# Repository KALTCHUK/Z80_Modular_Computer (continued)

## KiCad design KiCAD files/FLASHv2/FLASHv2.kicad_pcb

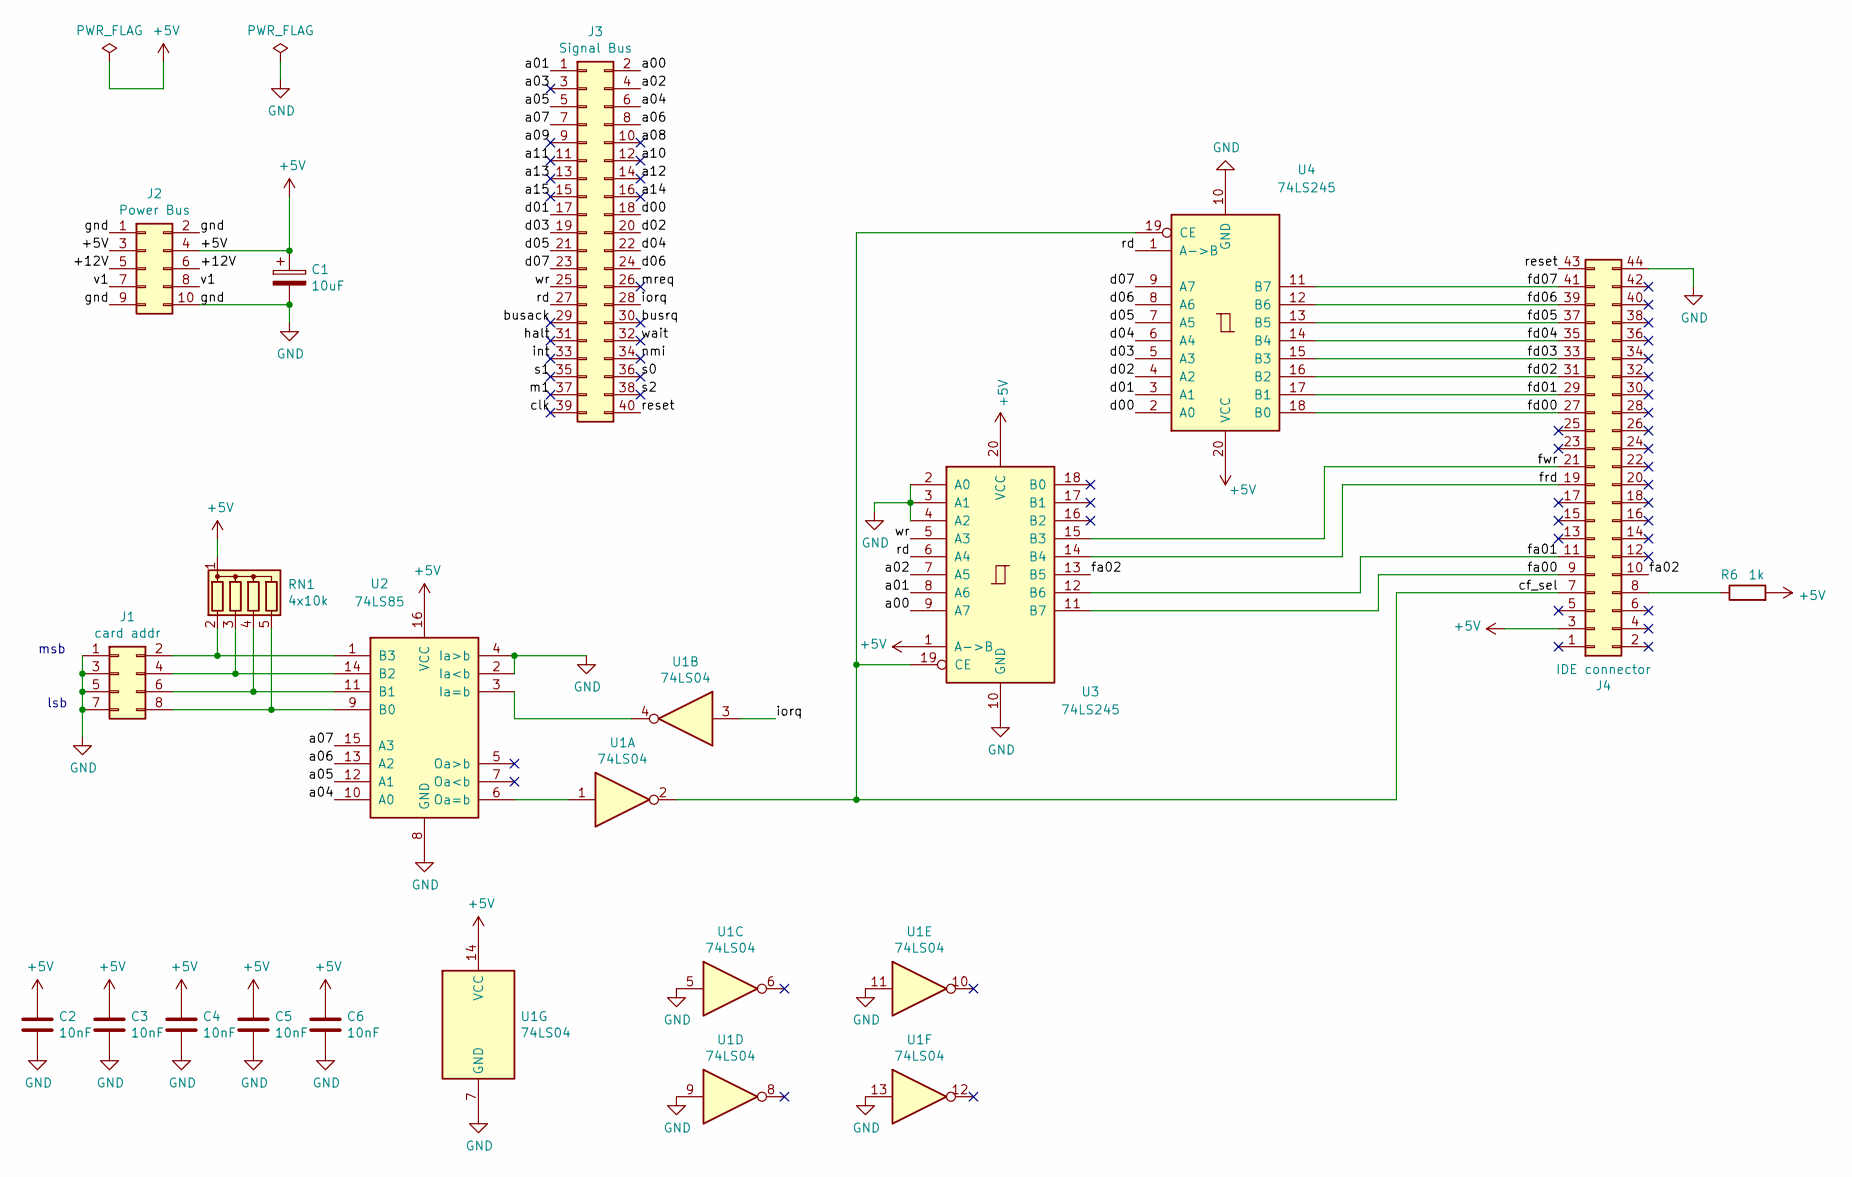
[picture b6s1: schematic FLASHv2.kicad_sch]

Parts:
C1: 10uF; CP_Radial_D5.0mm_P2.50mm
C2, C3, C4, C5, C6: 10nF; C_Disc_D3.8mm_W2.6mm_P2.50mm
J1: card addr; PinHeader_2x04_P2.54mm_Vertical
J2: Power Bus; PinHeader_2x05_P2.54mm_Vertical
J3: Signal Bus; PinHeader_2x20_P2.54mm_Vertical
J4: IDE connector; PinHeader_2x22_P2.00mm_Vertical
R6: 1k; R_Axial_DIN0207_L6.3mm_D2.5mm_P10.16mm_Horizontal
RN1: 4x10k; R_Array_SIP5
U1: 74LS04; DIP-14_W7.62mm_Socket_LongPads
U2: 74LS85; DIP-16_W7.62mm_Socket_LongPads
U3, U4: 74LS245; DIP-20_W7.62mm_Socket_LongPads

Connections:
+5V: C1.1, C2.1, C3.1, C4.1, C5.1, C6.1, J2.3, J2.4, J4.3, R6.2, RN1.1 (common), U1.14 (VCC), U2.16 (VCC), U3.1 (A->B), U3.20 (VCC), U4.20 (VCC)
/+12V: J2.5, J2.6
/a00: J3.2, U3.9 (A7)
/a01: J3.1, U3.8 (A6)
/a02: J3.4, U3.7 (A5)
/a03: J3.3
/a04: J3.6, U2.10 (A0)
/a05: J3.5, U2.12 (A1)
/a06: J3.8, U2.13 (A2)
/a07: J3.7, U2.15 (A3)
/a08: J3.10
/a09: J3.9
/a10: J3.12
/a11: J3.11
/a12: J3.14
/a13: J3.13
/a14: J3.16
/a15: J3.15
/busack: J3.29
/busrq: J3.30
/cf_sel: J4.7, U1.2, U3.19 (CE), U4.19 (CE)
/clk: J3.39
/d00: J3.18, U4.2 (A0)
/d01: J3.17, U4.3 (A1)
/d02: J3.20, U4.4 (A2)
/d03: J3.19, U4.5 (A3)
/d04: J3.22, U4.6 (A4)
/d05: J3.21, U4.7 (A5)
/d06: J3.24, U4.8 (A6)
/d07: J3.23, U4.9 (A7)
/fa00: J4.9, U3.11 (B7)
/fa01: J4.11, U3.12 (B6)
/fa02: J4.10, U3.13 (B5)
/fd00: J4.27, U4.18 (B0)
/fd01: J4.29, U4.17 (B1)
/fd02: J4.31, U4.16 (B2)
/fd03: J4.33, U4.15 (B3)
/fd04: J4.35, U4.14 (B4)
/fd05: J4.37, U4.13 (B5)
/fd06: J4.39, U4.12 (B6)
/fd07: J4.41, U4.11 (B7)
/frd: J4.19, U3.14 (B4)
/fwr: J4.21, U3.15 (B3)
/halt: J3.31
/int: J3.33
/iorq: J3.28, U1.3
/m1: J3.37
/mreq: J3.26
/nmi: J3.34
/rd: J3.27, U3.6 (A4), U4.1 (A->B)
/reset: J3.40, J4.43
/s0: J3.36
/s1: J3.35
/s2: J3.38
/v1: J2.7, J2.8
/wait: J3.32
/wr: J3.25, U3.5 (A3)
GND: C1.2, C2.2, C3.2, C4.2, C5.2, C6.2, J1.1, J1.3, J1.5, J1.7, J2.1, J2.2, J2.9, J2.10, J4.44, U1.5, U1.7 (GND), U1.9, U1.11, U1.13, U2.2 (Ia<b), U2.4 (Ia>b), U2.8 (GND), U3.2 (A0), U3.3 (A1), U3.4 (A2), U3.10 (GND), U4.10 (GND)
unnamed: J1.2, RN1.2 (R1), U2.1 (B3)
unnamed: J1.4, RN1.3 (R2), U2.14 (B2)
unnamed: J1.6, RN1.4 (R3), U2.11 (B1)
unnamed: J1.8, RN1.5 (R4), U2.9 (B0)
unnamed: J4.8, R6.1
unnamed: U1.1, U2.6 (Oa=b)
unnamed: U1.4, U2.3 (Ia=b)

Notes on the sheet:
lsb
msb

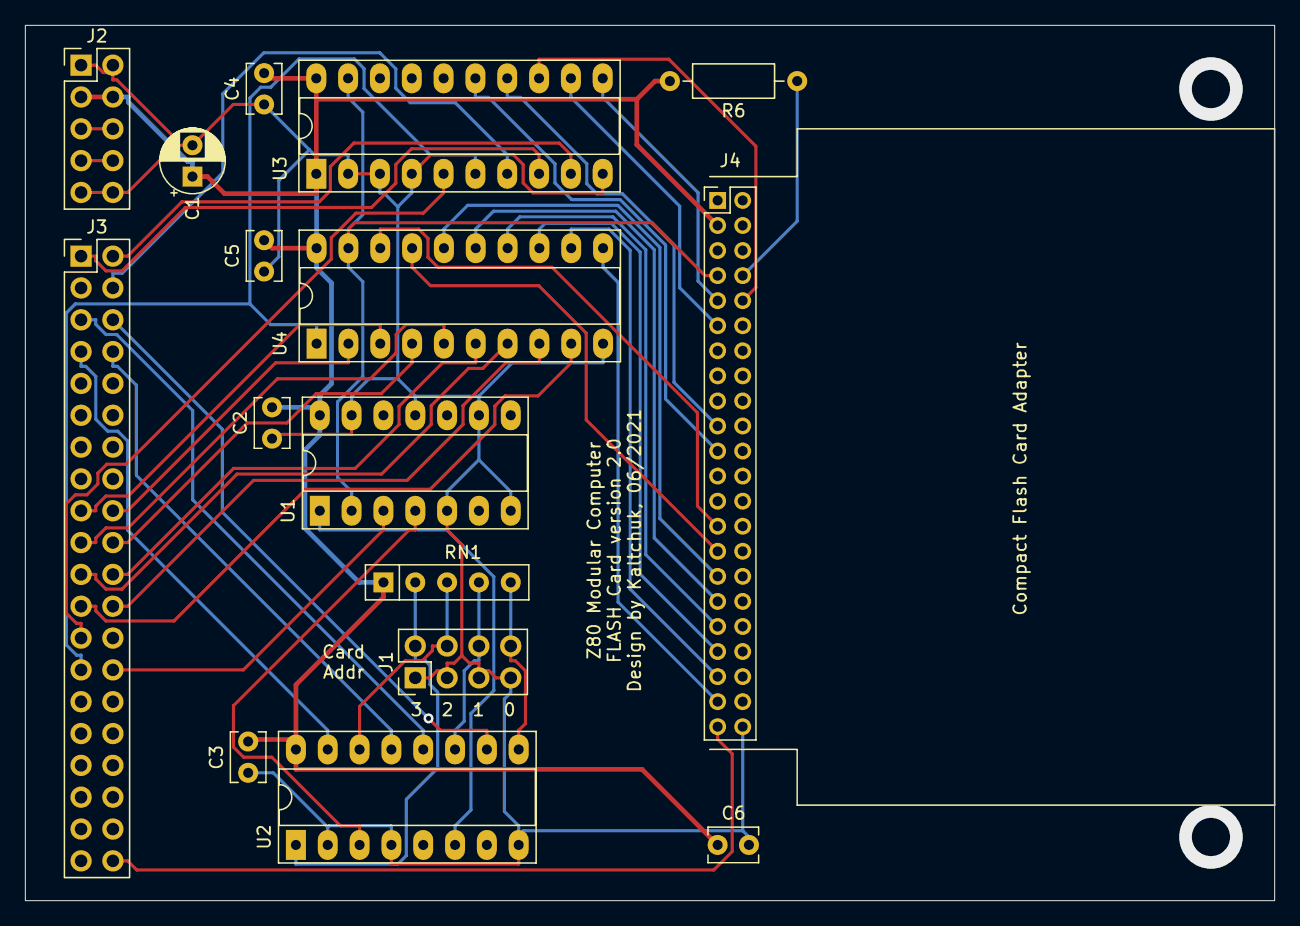
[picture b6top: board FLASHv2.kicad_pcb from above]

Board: 2 copper layers, 99.7 x 69.8 mm, 16 parts (0 on the bottom side), 44 nets.
